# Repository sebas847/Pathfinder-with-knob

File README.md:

# Pathfinder-with-knob
This device features a XIAO RP2040, 3 switches, and a knob. Each has its specific function configured via code.
This initial project was interesting for me, considering I don't have much knowledge about the subject. I was also drawn to the idea of ​​creating something that's actually useful in my daily life. I can configure the device so that each key acts as a shortcut or whatever, and the same goes for the knob I added. Plus, I learned how to make PCBs! I found creating my own PCB very interesting and satisfying; I had no idea they were made that way.
Here are some photos of the schematic and finished PCB.

And the scheme: 

Specs
Brain: Seeed Studio XIAO RP2040.

PCB Dimentions: 62.53 mm * 77.96 mm

Inputs: 3 Mechanics switches + 1 Encoder EC11 with bttn.

Outpots: 3 LEDs 

Voltage: 3.3V.

(BOM)

| Name | Purpose | Quantity | Total Cost (USD) | Link | Distributor |
| :--- | :--- | :---: | :---: | :--- | :--- |
| **Seeed Studio XIAO RP2040** | Microcontroller | 1 | $4.52 | [Link](https://es.aliexpress.com/item/1005006987582110.html) | Aliexpress |
| **Rotary Encoder (Knob)** | Rotary encoder with integrated push button. | 1 | $1.00 | [Link](https://es.aliexpress.com/item/1005009889978797.html) | Aliexpress |
| **PCB Pathfinder** | PCB board designed | 1 | $2.00 | [Link](https://jlcpcb.com/) | JLCPCB |
| **Mechanical Switches** | Mechanical switches for the keys.(I already have it) | 3 | $0.00 | [Link](https://es.aliexpress.com/item/1005006396423418.html) | Aliexpress |
| **LEDs** | Indicator LEDs (I already have it) | 3 | $0.00 | [Link](https://es.aliexpress.com/item/1005001414503004.html) | Aliexpress |
| **Resistors (220Ω - 330Ω)** | Resistors for LEDs (I already have it) | 3 | $0.00 | [Link](https://es.aliexpress.com/item/1005010049798113.html) | Aliexpress |

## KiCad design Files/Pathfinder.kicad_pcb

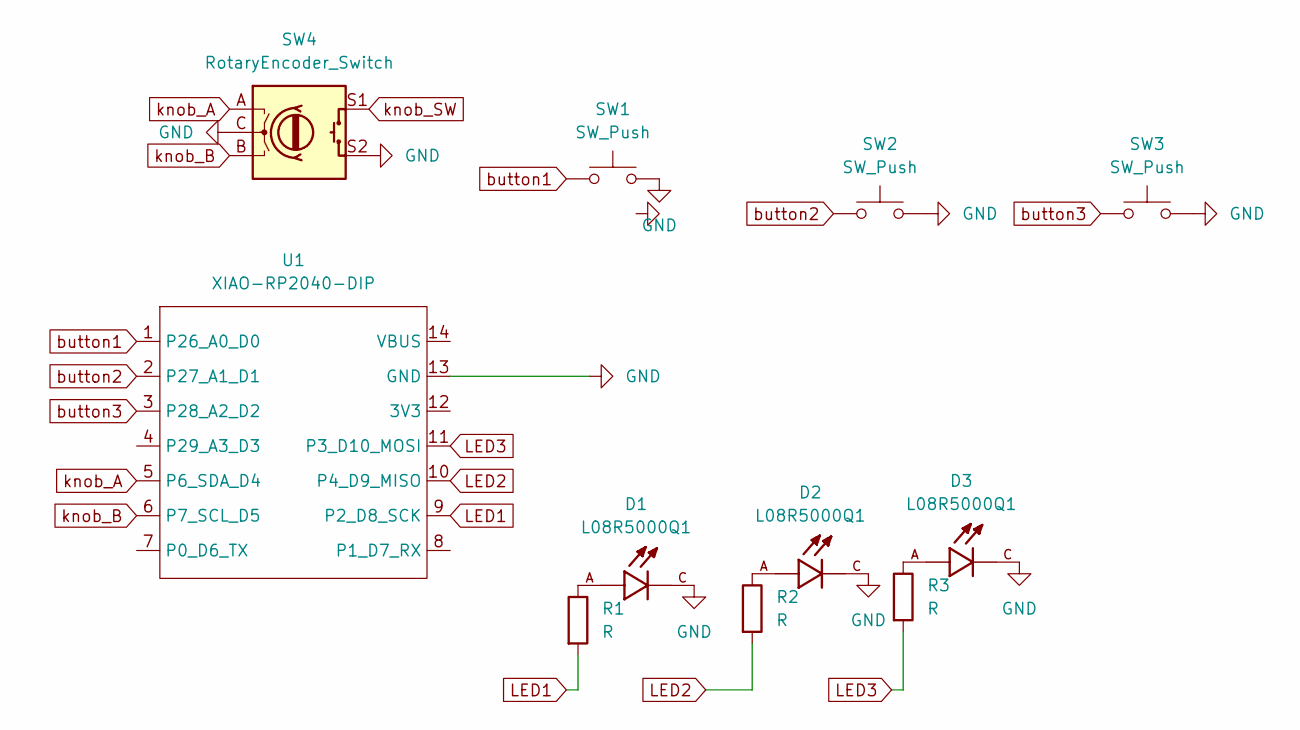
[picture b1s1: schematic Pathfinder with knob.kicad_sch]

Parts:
D1, D2, D3: L08R5000Q1; LEDRD254W57D500H1070; PARTREV NA
R1, R2, R3: R; R_Axial_DIN0204_L3.6mm_D1.6mm_P5.08mm_Vertical
SW1, SW2, SW3: SW_Push; SW_Cherry_MX_1.00u_PCB
SW4: RotaryEncoder_Switch; RotaryEncoder_Alps_EC11E-Switch_Vertical_H20mm
U1: XIAO-RP2040-DIP

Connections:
GND: D1.C, D2.C, D3.C, SW1.2, SW2.2, SW3.2, SW4.C, SW4.S2, U1.13 (GND)
LED1: R1.2, U1.9 (P2_D8_SCK)
LED2: R2.2, U1.10 (P4_D9_MISO)
LED3: R3.2, U1.11 (P3_D10_MOSI)
unnamed: D1.A, R1.1
unnamed: D2.A, R2.1
unnamed: D3.A, R3.1
button1: SW1.1, U1.1 (P26_A0_D0)
button2: SW2.1, U1.2 (P27_A1_D1)
button3: SW3.1, U1.3 (P28_A2_D2)
knob_A: SW4.A, U1.5 (P6_SDA_D4)
knob_B: SW4.B, U1.6 (P7_SCL_D5)
knob_SW: SW4.S1

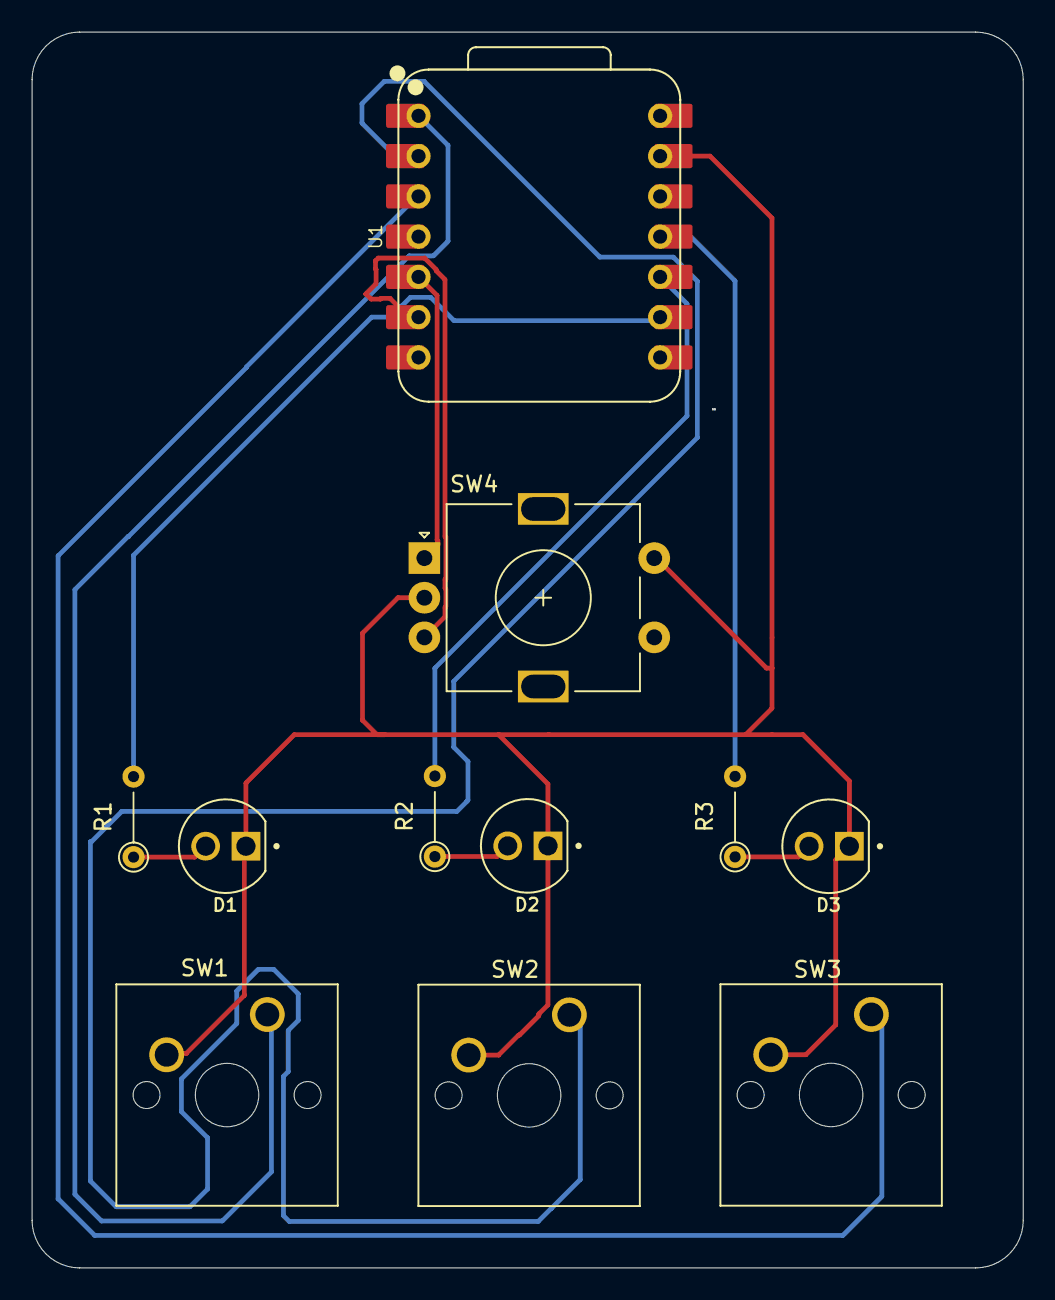
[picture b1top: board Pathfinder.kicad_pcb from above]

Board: 2 copper layers, 62.5 x 78.0 mm, 11 parts (0 on the bottom side), 12 nets.

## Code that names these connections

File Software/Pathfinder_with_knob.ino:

#include "Keyboard.h"


const int BUT1 = 26;    // P26_A0_D0
const int BUT2 = 27;    // P27_A1_D1
const int BUT3 = 28;    // P28_A2_D2

const int LED1 = 7;     // P1_D7_RX
const int LED2 = 9;     // P4_D9_MISO
const int LED3 = 10;    // P3_D10_MOSI

const int KNOB_A = 4;   // P6_SDA_D4
const int KNOB_B = 5;   // P7_SCL_D5
const int KNOB_SW = 29; // P29_A3_D3

void setup() {
  
  pinMode(BUT1, INPUT_PULLUP);
  pinMode(BUT2, INPUT_PULLUP);
  pinMode(BUT3, INPUT_PULLUP);
  pinMode(KNOB_SW, INPUT_PULLUP);
  pinMode(KNOB_A, INPUT_PULLUP);
  pinMode(KNOB_B, INPUT_PULLUP);

  
  pinMode(LED1, OUTPUT);
  pinMode(LED2, OUTPUT);
  pinMode(LED3, OUTPUT);

  Keyboard.begin();
}

void loop() {
  
  if (digitalRead(BUT1) == LOW) {
    digitalWrite(LED1, HIGH);
    Keyboard.press('a');
    delay(100);
    Keyboard.releaseAll();
  } else {
    digitalWrite(LED1, LOW);
  }


}

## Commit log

2026-05-03 Create Gerbers
